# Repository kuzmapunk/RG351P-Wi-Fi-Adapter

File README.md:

# RG351P-Wi-Fi-Adapter
RG351P adapter based on BL-M7601NU4 module board
</br>

#### Compatible modules:
  - **HLK-7601U2** - folder **RTL8188EUS**
  - **BL-R7601MU2** - folder **RTL8188EUS**
  - **RTL8188EUS** - folder **RTL8188EUS**
  - **RL-UM12BS-8188EUS** - folder **RTL8188EUS**
  - [WIP] **BL-R7601MU6** - folder **BL-R7601MU6**

#### Footprints(folder **RTL8188EUS**):

#### Footprints(folder **BL-R7601MU6**):
[WIP]

#### Photos of prototype PCB:

#### Inside RG351P:

#### UPDATES:
 - Move project file to folder with compatible module name.
 - Update castelated holes

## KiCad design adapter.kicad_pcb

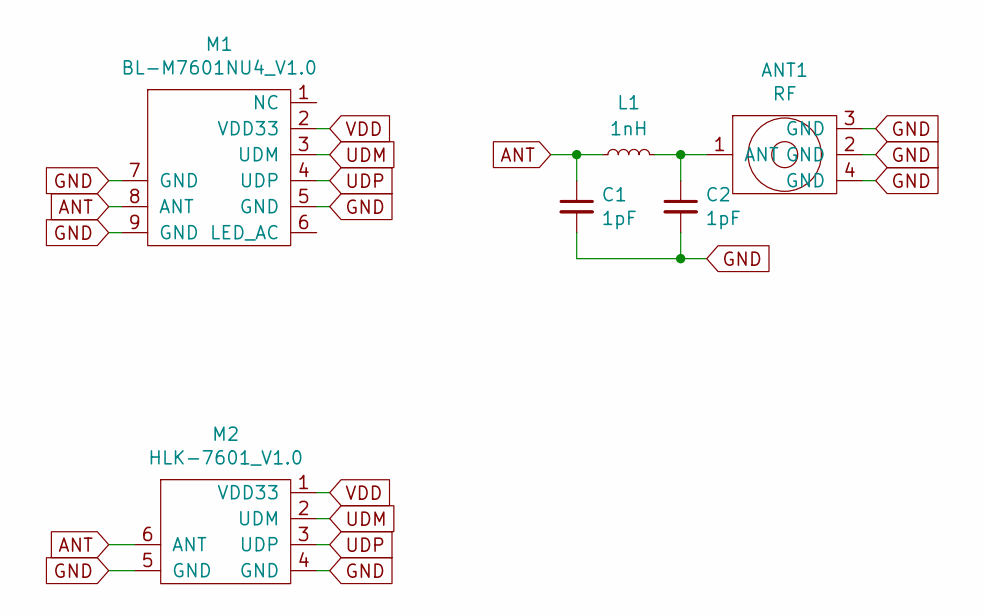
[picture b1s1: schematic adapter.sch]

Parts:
ANT1: RF; COAXIAL_CONN
C1, C2: 1pF; C_0402_1005Metric
L1: 1nH; L_0402_1005Metric
M1: BL-M7601NU4_V1.0
M2: HLK-7601_V1.0

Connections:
ANT: C1.1, L1.1, M1.8 (ANT), M2.6 (ANT)
GND: ANT1.2 (GND), ANT1.3 (GND), ANT1.4 (GND), C1.2, C2.2, M1.5 (GND), M1.7 (GND), M1.9 (GND), M2.4 (GND), M2.5 (GND)
unnamed: ANT1.1 (ANT), C2.1, L1.2
UDM: M1.3 (UDM), M2.2 (UDM)
UDP: M1.4 (UDP), M2.3 (UDP)
VDD: M1.2 (VDD33), M2.1 (VDD33)

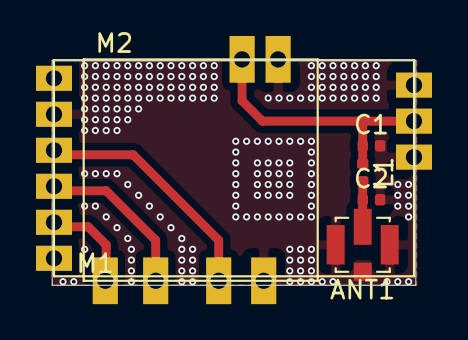
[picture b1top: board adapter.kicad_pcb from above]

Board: 2 copper layers, 20.2 x 12.5 mm, 6 parts (0 on the bottom side), 6 nets.

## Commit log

2021-01-24 Add files to project
2021-01-24 Update README.md Add change to PCB
2021-01-24 Edit: README.md
2021-01-24 Edit images
2021-01-27 modified: README.md renamed: adapter-cache.lib -> RTL8188EUS/adapter-cache.lib new file: RTL8188EUS/adapter.kicad_pcb renamed: adapter.pro -> RTL8188EUS/adapter.pro renamed: adapter.sch -> RTL8188EUS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
2021-02-03 new file: BL-R7601MU6/adapter-cache.lib new file: BL-R7601MU6/adapter.kicad_pcb new file: BL-R7601MU6/adapter.pro new file: BL-R7601MU6/adapter.sch new file: BL-R7601MU6/components.dcm new file: BL-R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
